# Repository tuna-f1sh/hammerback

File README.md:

# Hammerback - Battery Backpack for Hammerhead Karoo 2

A quick prototype to expand the battery of the Hammerhead Karoo 2 by attaching a larger battery between the device and handlebar mount.

It is essentially a [Adafruit Powerboost 1000C](https://www.adafruit.com/product/2465) in a layout with vertical USB-C to the Karoo 2 and a side USB-C for charging. The _backpack_ contains a LiPo (that connects to the PCB), Karoo 2 style mount and quarter turn at the base for attaching to bike. It is secured by taking the place of the USB-C cover plate with extended T8 screws.

## Photos

**Not my best soldering!**

**Made some nice silkscreen art 😁**

## Project State

I put this together quickly as an idea. Whilst it worked in principle, it could do with some refining. I also have other ideas that could be included:

* Illumination - use the LiPo as a supply for a small front light if a transparent backpack is used.
* Switch for turning on/off. Currently it will supply the Karoo until the LiPo is empty or one must to remove it.
* The design could also be simplified to simply be the vertical USB-C to Karoo, with a header for a 5 V source - this could be used with an existing battery pack rather so using that BMS/charging rather than on-board.

# Mechanicals

[Fusion 360 design](https://a360.co/3pR5RNK)

# Disclaimer

It should be obvious but this is supplied without warranty and to be used at user's discretion. Always be careful when using LiPo cells. I cannot guarantee the working state of this.

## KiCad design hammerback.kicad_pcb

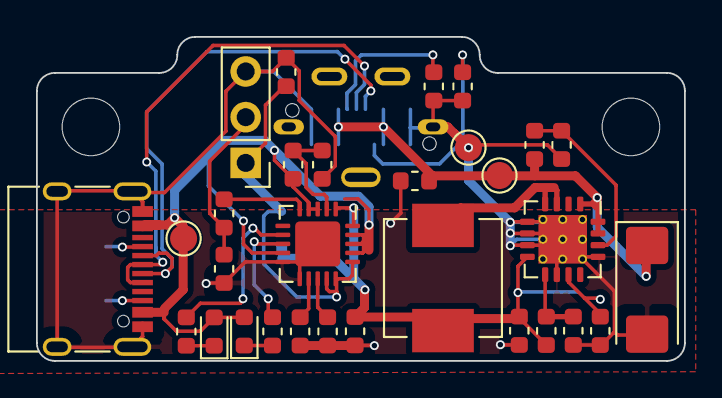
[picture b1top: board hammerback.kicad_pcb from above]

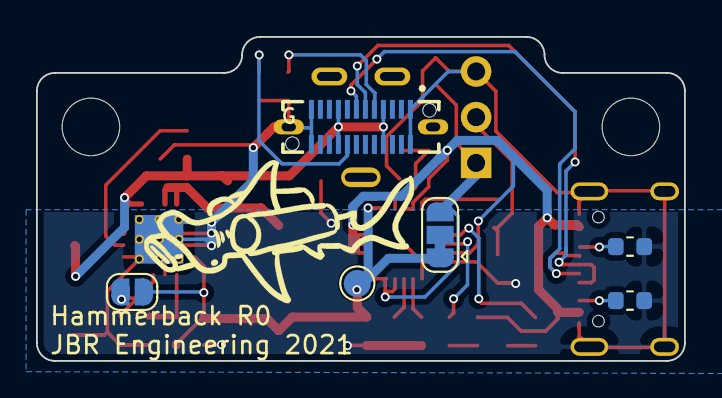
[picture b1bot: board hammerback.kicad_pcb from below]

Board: 2 copper layers, 36.0 x 18.0 mm, 38 parts (6 on the bottom side), 24 nets.

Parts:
C1, C2: 10u; C_0603_1608Metric
C3: 100n; C_0603_1608Metric
C4: 2.2u; C_0603_1608Metric
C5: 100u; CP_EIA-6032-20_AVX-F
D1: CHARGE; LED_0603_1608Metric
D2: DONE; LED_0603_1608Metric
H1, H2: MountingHole; MountingHole_3.2mm_M3_ISO14580
J2: LiPo; PinHeader_1x03_P2.54mm_Vertical
JP1: SolderJumper_3_Bridged12; SolderJumper-3_P1.3mm_Bridged12_RoundedPad1.0x1.5mm
JP2: SolderJumper_2_Open; SolderJumper-2_P1.3mm_Open_RoundedPad1.0x1.5mm
L1: 6.8uH; L_Vishay_IHLP-2525
P1: USB_C_Plug_USB2.0; GCT_USB4151-GF-C_REVA
R1, R2: 1k; R_0603_1608Metric
R3: 270k; R_0603_1608Metric
R4: 100k; R_0603_1608Metric
R5, R7, R10: 1k54; R_0603_1608Metric
R6: 69k8; R_0603_1608Metric
R8, R9, R14, R15: 5k1; R_0603_1608Metric
R11: 1.87M; R_0603_1608Metric
R12: 340k; R_0603_1608Metric
R13: 10k; R_0603_1608Metric
R16: 2M; R_0603_1608Metric
R17: 200k; R_0603_1608Metric
TP1, TP2, TP3, TP4: TestPoint; TestPoint_Pad_D1.5mm
U1: MCP73871; QFN-20-1EP_4x4mm_P0.5mm_EP2.5x2.5mm
U2: TPS61090; Texas_S-PVQFN-N16_EP2.7x2.7mm_ThermalVias
ee1: USB_C_Receptacle_USB2.0; USB_C_Receptacle_XKB_U262-16XN-4BVC11

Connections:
+5V: C4.1, C5.1, P1.A4, P1.A9, P1.B4, P1.B9, R16.1, TP4.1, U2.1, U2.15, U2.16
/BOOST: JP2.1, R13.1, U2.11
/NTC: J2.2, R5.2, R6.1
/STAT1: R7.2, U1.8
/STAT2: R10.2, U1.7
/USB_N: P1.A7, ee1.A7, ee1.B7
/USB_P: P1.A6, ee1.A6, ee1.B6
GND: C1.2, C2.2, C3.2, C4.2, C5.2, J2.3, P1.A1, P1.A12, P1.B1, P1.B12, P1.S1, R1.2, R2.2, R4.2, R6.2, R8.1, R9.1, R12.2, R13.2, R14.1, R15.1, R17.2, TP1.1, U1.10, U1.11, U1.21, U2.5, U2.6, U2.7, U2.10, U2.13, U2.17, ee1.A1, ee1.A12, ee1.B1, ee1.B12, ee1.S1
unnamed: C1.1, J2.1, JP1.3, U1.14, U1.15, U1.16
unnamed: C2.1, C3.1, JP1.1, JP2.2, L1.1, R11.1, TP3.1, U1.1, U1.20, U2.8
unnamed: D1.1, R7.1
unnamed: D2.1, R10.1
unnamed: L1.2, U2.3, U2.4
unnamed: P1.A5, R14.2
unnamed: P1.B5, R15.2
unnamed: R1.1, U1.13
unnamed: R2.1, U1.12
unnamed: R3.2, R4.1, U1.2
unnamed: R5.1, U1.5
unnamed: R8.2, ee1.B5
unnamed: R9.2, ee1.A5
unnamed: R11.2, R12.1, U2.9
unnamed: R16.2, R17.1, U2.14
VBUS: D1.2, D2.2, R3.1, TP2.1, U1.3, U1.4, U1.9, U1.17, U1.18, U1.19, ee1.A4, ee1.A9, ee1.B4, ee1.B9

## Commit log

2021-07-15 breakout for vertical plug
2021-07-29 fix hole size in pad
2022-03-30 pcb updates
2023-05-18 update for kicad 7
2023-05-18 README
2023-05-18 build workflow
2023-05-18 fix build
2023-05-18 add LICENSE
2023-05-18 permission for workflow
2023-05-18 only make pdf
